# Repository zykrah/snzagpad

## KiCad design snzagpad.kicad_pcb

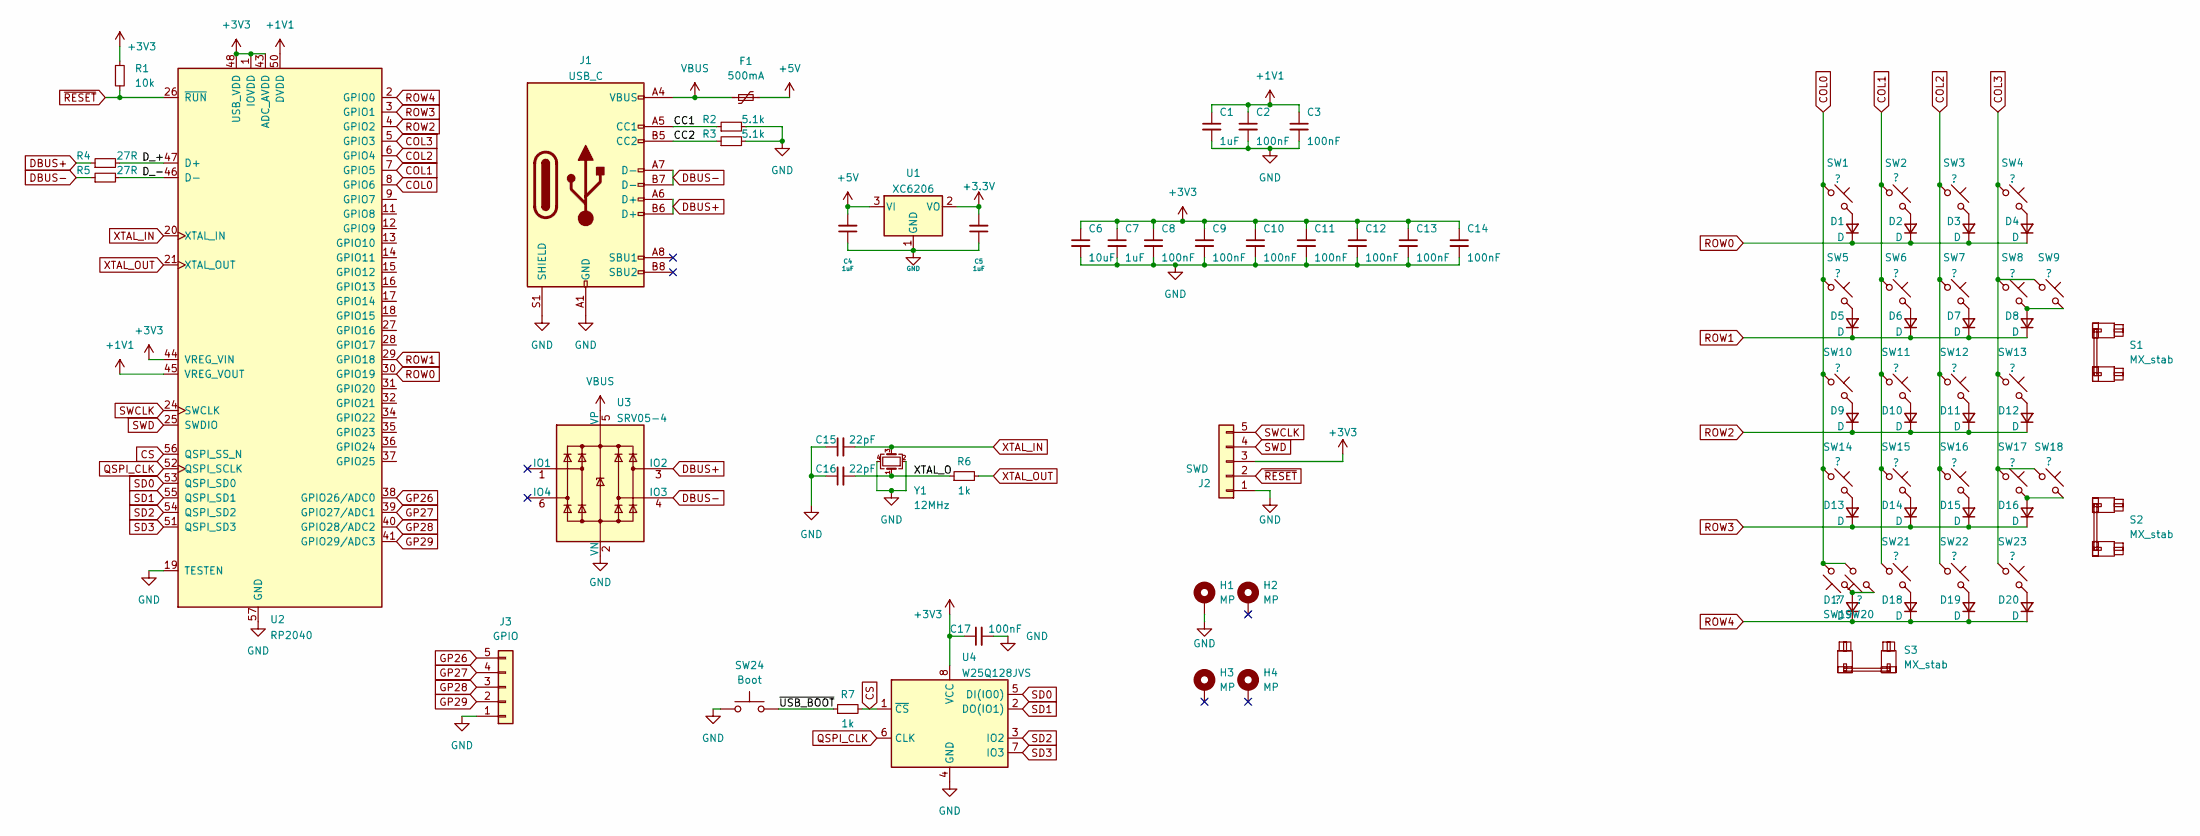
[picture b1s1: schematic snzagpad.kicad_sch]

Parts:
C1, C4, C5, C7: 1uF; C_0402_1005Metric; LCSC C52923
C2, C3, C8, C9, C10, C11, C12, C13, C14, C17: 100nF; C_0402_1005Metric; LCSC C1525
C6: 10uF; C_0402_1005Metric; LCSC C15525
C15, C16: 22pF; C_0402_1005Metric; LCSC C1555
D1, D2, D3, D4, D5, D6, D7, D8, D9, D10, D11, D12, D13, D14, D15, D16, D17, D18, D19, D20: D; D_SOD-123; LCSC C81598
F1: 500mA; Fuse_1206_3216Metric; LCSC C70076
H1, H2, H3, H4: MP; MountingHole_2.2mm_M2_ISO14580_Pad
J1: USB_C; USB_C_Receptacle_HRO_TYPE-C-31-M-12; LCSC C2982555
J2: SWD; PinSocket_1x05_P2.54mm_Vertical
J3: GPIO; PinHeader_1x05_P1.00mm_Vertical
R1: 10k; R_0402_1005Metric; LCSC C25744
R2, R3: 5.1k; R_0402_1005Metric; LCSC C25905
R4, R5: 27R; R_0603_1608Metric; LCSC C25190
R6, R7: 1k; R_0402_1005Metric; LCSC C11702
S1, S2, S3: MX_stab; STAB_MX_2u
SW1, SW2, SW3, SW4, SW5, SW6, SW7, SW8, SW9, SW10, SW11, SW12, SW13, SW14, SW15, SW16, SW17, SW18, SW19, SW20, SW21, SW22, SW23: ?; SW_MX_HS_1u; LCSC C2803348
SW24: Boot; PinSocket_1x02_P2.54mm_Vertical
U1: XC6206; SOT-23; LCSC C5446
U2: RP2040; RP2040-QFN-56; LCSC C2040
U3: SRV05-4; SOT-23-6-routable; LCSC C85364
U4: W25Q128JVS; SOIC-8_5.23x5.23mm_P1.27mm; LCSC C97521
Y1: 12MHz; Crystal_SMD_3225-4Pin_3.2x2.5mm; LCSC C9002

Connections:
+1V1: C1.1, C2.1, C3.1, U2.23 (DVDD), U2.45 (VREG_VOUT), U2.50 (DVDD)
+5V: C4.2, F1.2, U1.3 (VI)
/CC1: J1.A5 (CC1), R2.1
/CC2: J1.B5 (CC2), R3.1
/D_+: R4.2, U2.47 (D+)
/D_-: R5.2, U2.46 (D-)
/XTAL_O: C16.2, R6.1, Y1.1
/~USB_BOOT: R7.1, SW24.2
COL0: SW1.1, SW5.1, SW10.1, SW14.1, SW19.2, SW20.2, U2.8 (GPIO6)
COL1: SW2.1, SW6.1, SW11.1, SW15.1, SW21.1, U2.7 (GPIO5)
COL2: SW3.1, SW7.1, SW12.1, SW16.1, SW22.1, U2.6 (GPIO4)
COL3: SW4.1, SW8.1, SW9.1, SW13.1, SW17.1, SW18.1, SW23.1, U2.5 (GPIO3)
CS: R7.2, U2.56 (QSPI_SS_N), U4.1 (~CS)
DBUS+: J1.A6 (D+), J1.B6 (D+), R4.1, U3.3 (IO2)
DBUS-: J1.A7 (D-), J1.B7 (D-), R5.1, U3.4 (IO3)
GND: C1.2, C2.2, C3.2, C4.1, C5.1, C6.2, C7.2, C8.2, C9.2, C10.2, C11.2, C12.2, C13.2, C14.2, C15.1, C16.1, C17.2, H1.1, J1.A1 (GND), J1.A12 (GND), J1.B1 (GND), J1.B12 (GND), J1.S1 (SHIELD), J2.1, J3.1, R2.2, R3.2, SW24.1, U1.1 (GND), U2.19 (TESTEN), U2.57 (GND), U3.2 (VN), U4.4 (GND), Y1.2, Y1.4
GP26: J3.5, U2.38 (GPIO26/ADC0)
GP27: J3.4, U2.39 (GPIO27/ADC1)
GP28: J3.3, U2.40 (GPIO28/ADC2)
GP29: J3.2, U2.41 (GPIO29/ADC3)
unnamed: D1.2 (A), SW1.2
unnamed: D2.2 (A), SW2.2
unnamed: D3.2 (A), SW3.2
unnamed: D4.2 (A), SW4.2
unnamed: D5.2 (A), SW5.2
unnamed: D6.2 (A), SW6.2
unnamed: D7.2 (A), SW7.2
unnamed: D8.2 (A), SW8.2, SW9.2
unnamed: D9.2 (A), SW10.2
unnamed: D10.2 (A), SW11.2
unnamed: D11.2 (A), SW12.2
unnamed: D12.2 (A), SW13.2
unnamed: D13.2 (A), SW14.2
unnamed: D14.2 (A), SW15.2
unnamed: D15.2 (A), SW16.2
unnamed: D16.2 (A), SW17.2, SW18.2
unnamed: D17.2 (A), SW19.1, SW20.1
unnamed: D18.2 (A), SW21.2
unnamed: D19.2 (A), SW22.2
unnamed: D20.2 (A), SW23.2
QSPI_CLK: U2.52 (QSPI_SCLK), U4.6 (CLK)
ROW0: D1.1 (K), D2.1 (K), D3.1 (K), D4.1 (K), U2.30 (GPIO19)
ROW1: D5.1 (K), D6.1 (K), D7.1 (K), D8.1 (K), U2.29 (GPIO18)
ROW2: D9.1 (K), D10.1 (K), D11.1 (K), D12.1 (K), U2.4 (GPIO2)
ROW3: D13.1 (K), D14.1 (K), D15.1 (K), D16.1 (K), U2.3 (GPIO1)
ROW4: D17.1 (K), D18.1 (K), D19.1 (K), D20.1 (K), U2.2 (GPIO0)
SD0: U2.53 (QSPI_SD0), U4.5 (DI(IO0))
SD1: U2.55 (QSPI_SD1), U4.2 (DO(IO1))
SD2: U2.54 (QSPI_SD2), U4.3 (IO2)
SD3: U2.51 (QSPI_SD3), U4.7 (IO3)
SWCLK: J2.5, U2.24 (SWCLK)
SWD: J2.4, U2.25 (SWDIO)
VBUS: F1.1, J1.A4 (VBUS), J1.A9 (VBUS), J1.B4 (VBUS), J1.B9 (VBUS), U3.5 (VP)
XTAL_IN: C15.2, U2.20 (XTAL_IN), Y1.3
XTAL_OUT: R6.2, U2.21 (XTAL_OUT)
~RESET: J2.2, R1.2, U2.26 (~RUN)

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
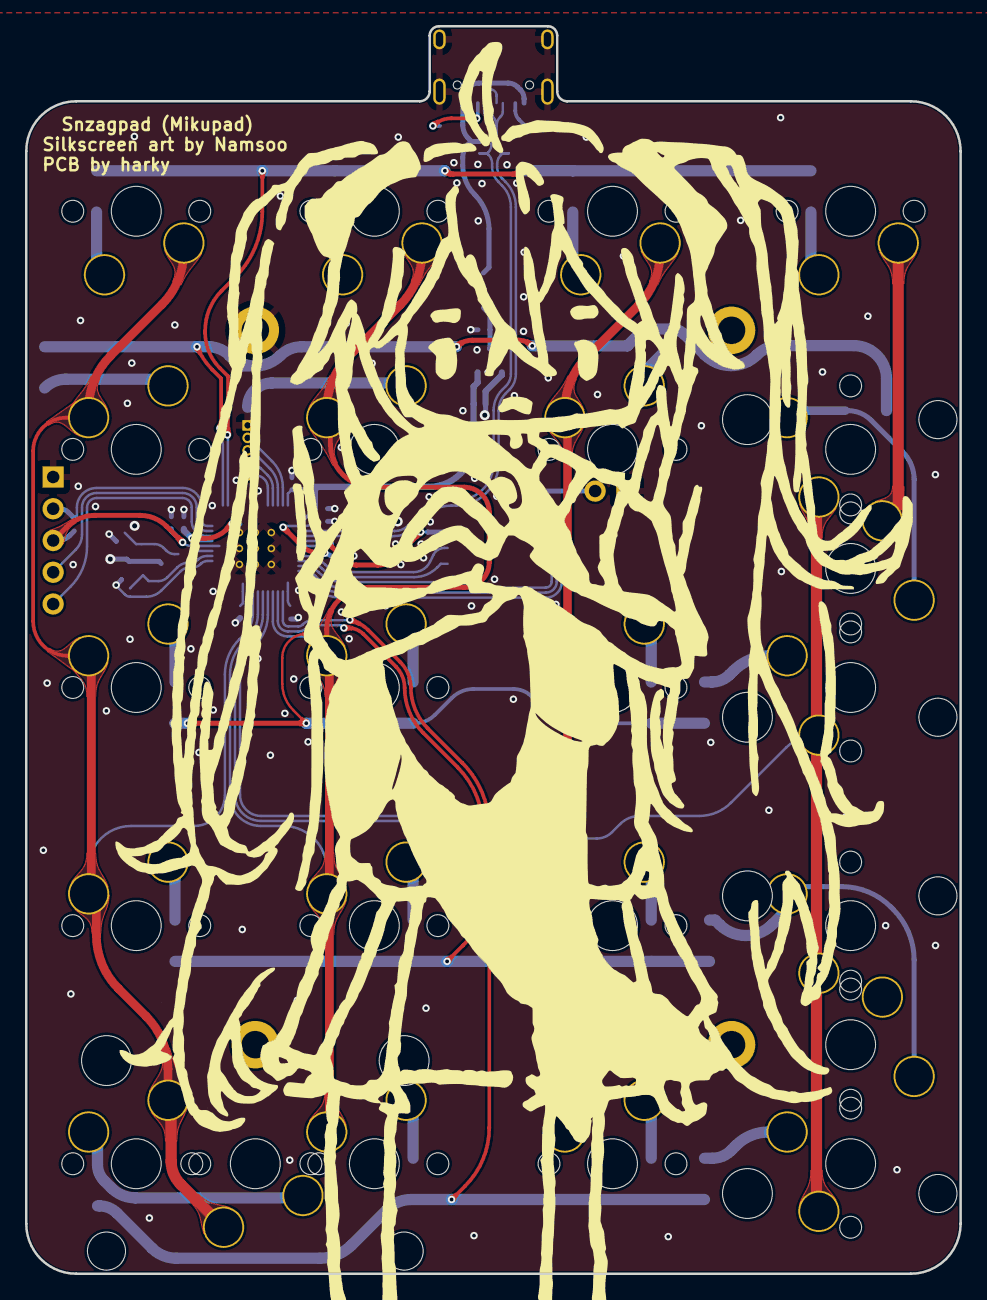
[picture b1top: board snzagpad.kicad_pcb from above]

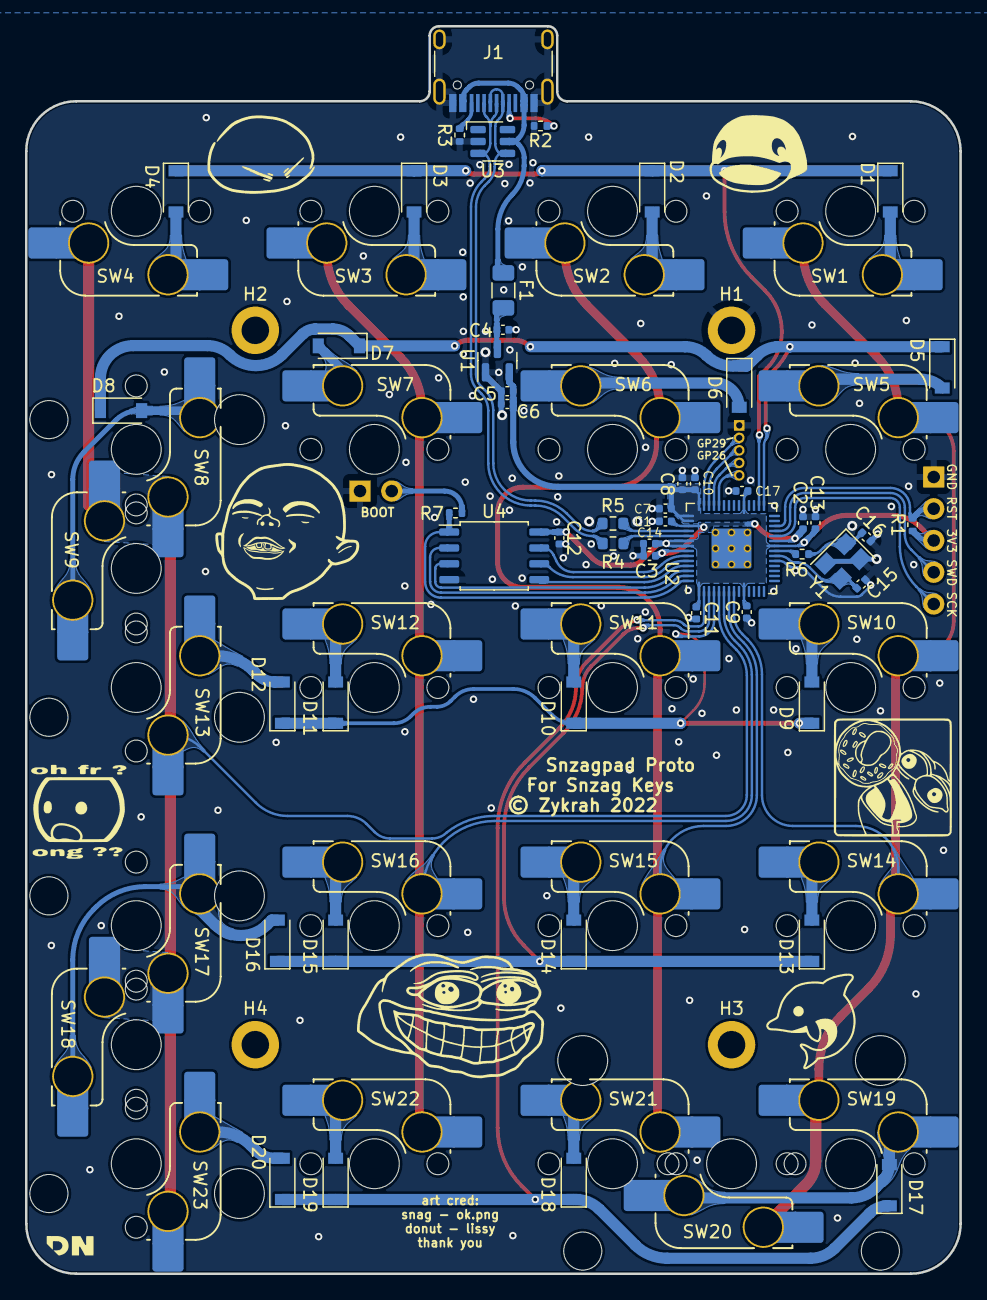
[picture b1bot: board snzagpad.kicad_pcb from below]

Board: 2 copper layers, 74.8 x 99.8 mm, 84 parts (78 on the bottom side), 57 nets.

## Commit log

2022-08-04 Initial project setup
2022-08-04 Initial Draft
    Added sleep lib, created schematic with base components, imported into PCB and began preliminary routing
2022-08-14 Updated outline, added mounts, preliminary routing
2022-08-14 Edited cutout, mounts, USB position, routing
2022-08-15 Completed mostly, rounded traces, connected everything
2022-08-16 Updated outline, more silkscreens
2022-08-17 More silkscreen additions/modification, added teardrops
2022-08-17 Prototype manufacturing files
2022-08-17 Added GPIO breakout
2022-12-28 Minor change, updated manufacturing files, added step file

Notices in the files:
snzagpad.kicad_pcb:
© Zykrah 2022
